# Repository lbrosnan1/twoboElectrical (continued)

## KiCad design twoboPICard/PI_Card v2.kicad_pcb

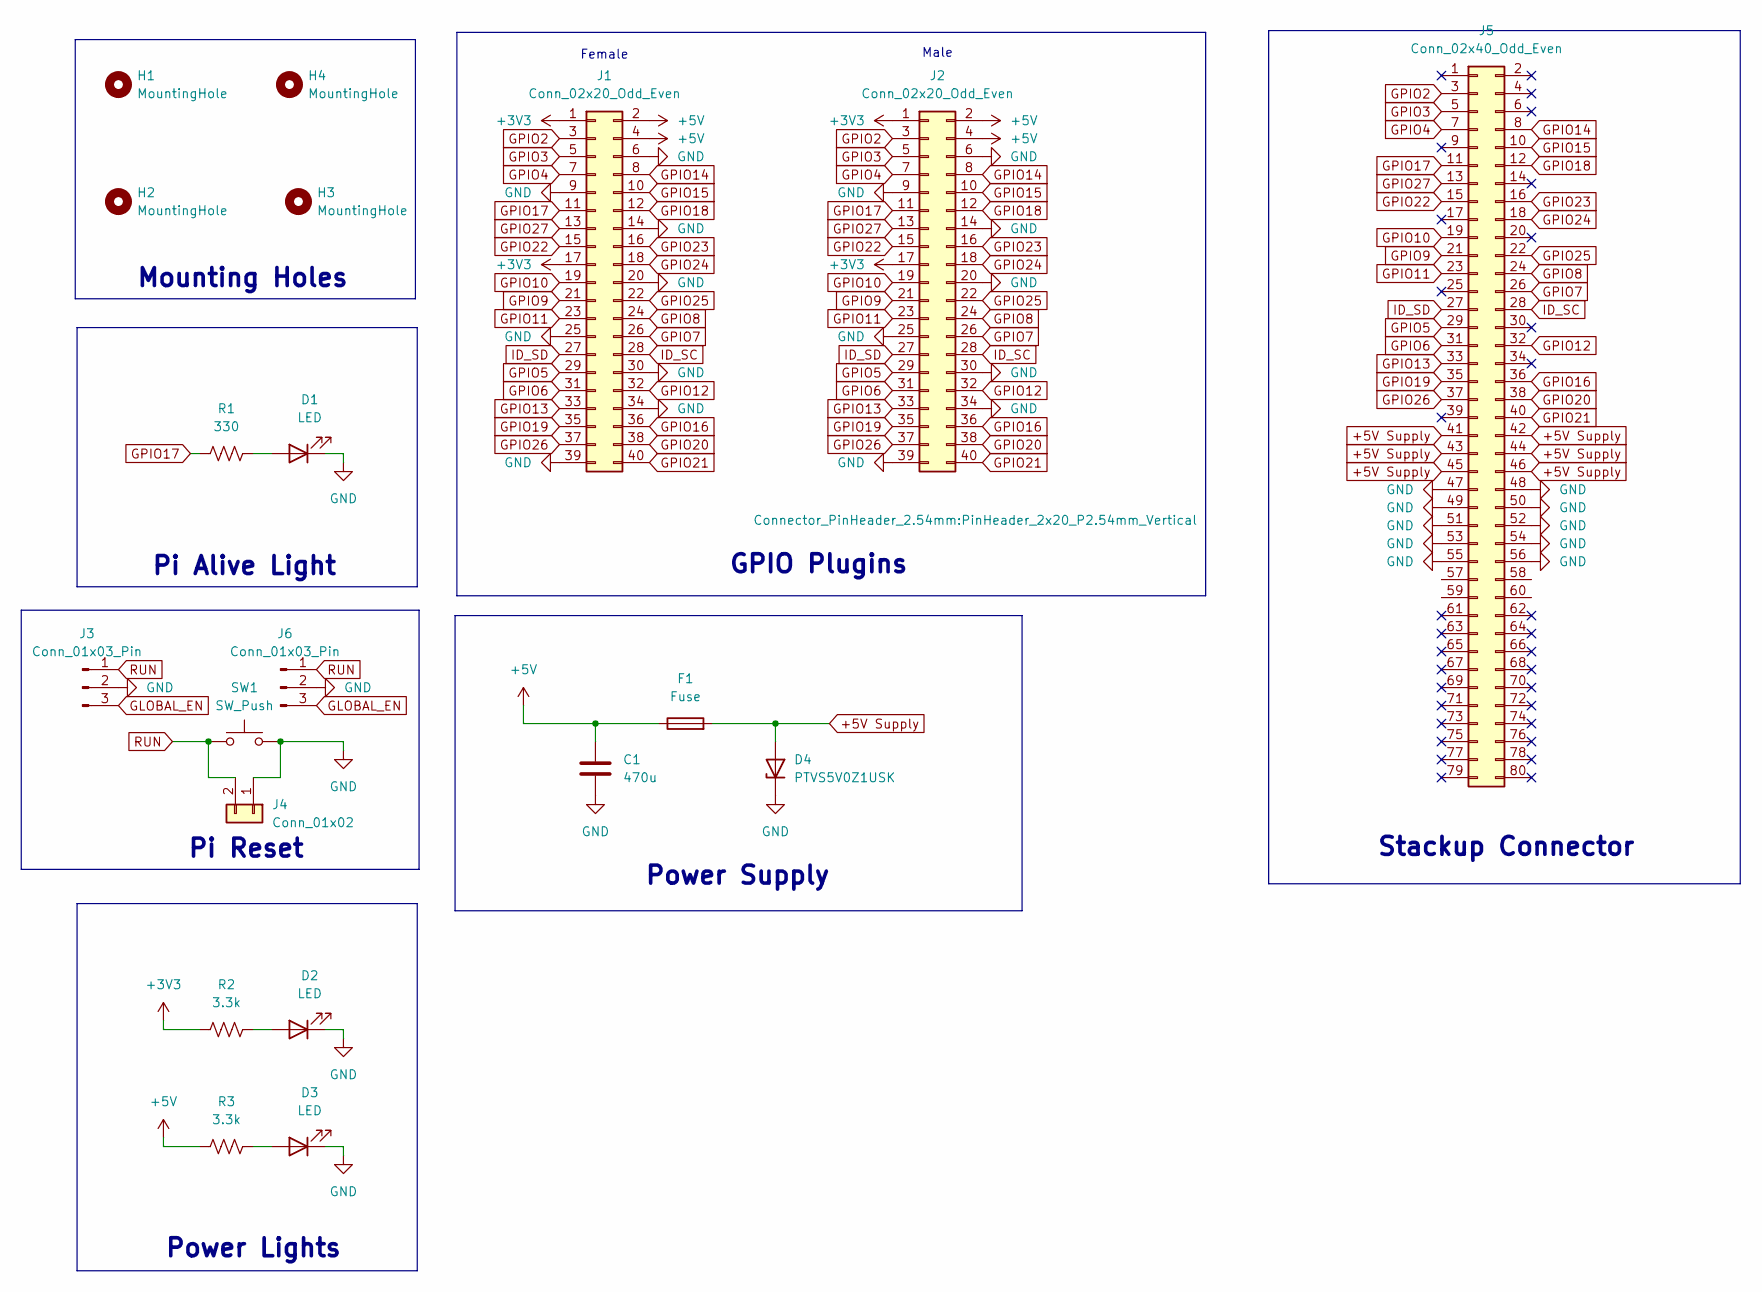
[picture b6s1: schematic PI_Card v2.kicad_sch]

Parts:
C1: 470u; CP_Radial_D10.0mm_P5.00mm
D1, D2, D3: LED; LED_D5.0mm
D4: PTVS5V0Z1USK; Nexperia_DSN1608-2_1.6x0.8mm
F1: Fuse; Fuseholder_Littelfuse_Nano2_154x_3D
H1, H2, H3, H4: MountingHole; MountingHole_3.2mm_M3
J1: Conn_02x20_Odd_Even; PinSocket_2x20_P2.54mm_Vertical
J2: Conn_02x20_Odd_Even; PinHeader_2x20_P2.54mm_Vertical
J3, J6: Conn_01x03_Pin; PinHeader_1x03_P2.54mm_Vertical
J4: Conn_01x02; JST_PH_B2B-PH-K_1x02_P2.00mm_Vertical
J5: Conn_02x40_Odd_Even; Samtec_HLE-140-02-L-DV-PE_2x40_P2.54mm_Horizontal
R1: 330; R_0805_2012Metric_Pad1.20x1.40mm_HandSolder
R2, R3: 3.3k; R_0805_2012Metric_Pad1.20x1.40mm_HandSolder
SW1: SW_Push; SW_PUSH_6mm

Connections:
+3V3: J1.1, J1.17, J2.1, J2.17, R2.1
+5V: C1.1, F1.1, J1.2, J1.4, J2.2, J2.4, R3.1
+5V Supply: D4.2 (A), F1.2, J5.41, J5.42, J5.43, J5.44, J5.45, J5.46
GLOBAL_EN: J3.3, J6.3
GND: C1.2, D1.1 (K), D2.1 (K), D3.1 (K), D4.1 (K), J1.6, J1.9, J1.14, J1.20, J1.25, J1.30, J1.34, J1.39, J2.6, J2.9, J2.14, J2.20, J2.25, J2.30, J2.34, J2.39, J3.2, J4.1, J5.47, J5.48, J5.49, J5.50, J5.51, J5.52, J5.53, J5.54, J5.55, J5.56, J6.2, SW1.2
GPIO2: J1.3, J2.3, J5.3
GPIO3: J1.5, J2.5, J5.5
GPIO4: J1.7, J2.7, J5.7
GPIO5: J1.29, J2.29, J5.29
GPIO6: J1.31, J2.31, J5.31
GPIO7: J1.26, J2.26, J5.26
GPIO8: J1.24, J2.24, J5.24
GPIO9: J1.21, J2.21, J5.21
GPIO10: J1.19, J2.19, J5.19
GPIO11: J1.23, J2.23, J5.23
GPIO12: J1.32, J2.32, J5.32
GPIO13: J1.33, J2.33, J5.33
GPIO14: J1.8, J2.8, J5.8
GPIO15: J1.10, J2.10, J5.10
GPIO16: J1.36, J2.36, J5.36
GPIO17: J1.11, J2.11, J5.11, R1.1
GPIO18: J1.12, J2.12, J5.12
GPIO19: J1.35, J2.35, J5.35
GPIO20: J1.38, J2.38, J5.38
GPIO21: J1.40, J2.40, J5.40
GPIO22: J1.15, J2.15, J5.15
GPIO23: J1.16, J2.16, J5.16
GPIO24: J1.18, J2.18, J5.18
GPIO25: J1.22, J2.22, J5.22
GPIO26: J1.37, J2.37, J5.37
GPIO27: J1.13, J2.13, J5.13
ID_SC: J1.28, J2.28, J5.28
ID_SD: J1.27, J2.27, J5.27
unnamed: D1.2 (A), R1.2
unnamed: D2.2 (A), R2.2
unnamed: D3.2 (A), R3.2
RUN: J3.1, J4.2, J6.1, SW1.1

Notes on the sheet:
Female
Power Supply
Pi Reset
GPIO Plugins
Stackup Connector
Power Lights
Pi Alive Light
Male
Mounting Holes

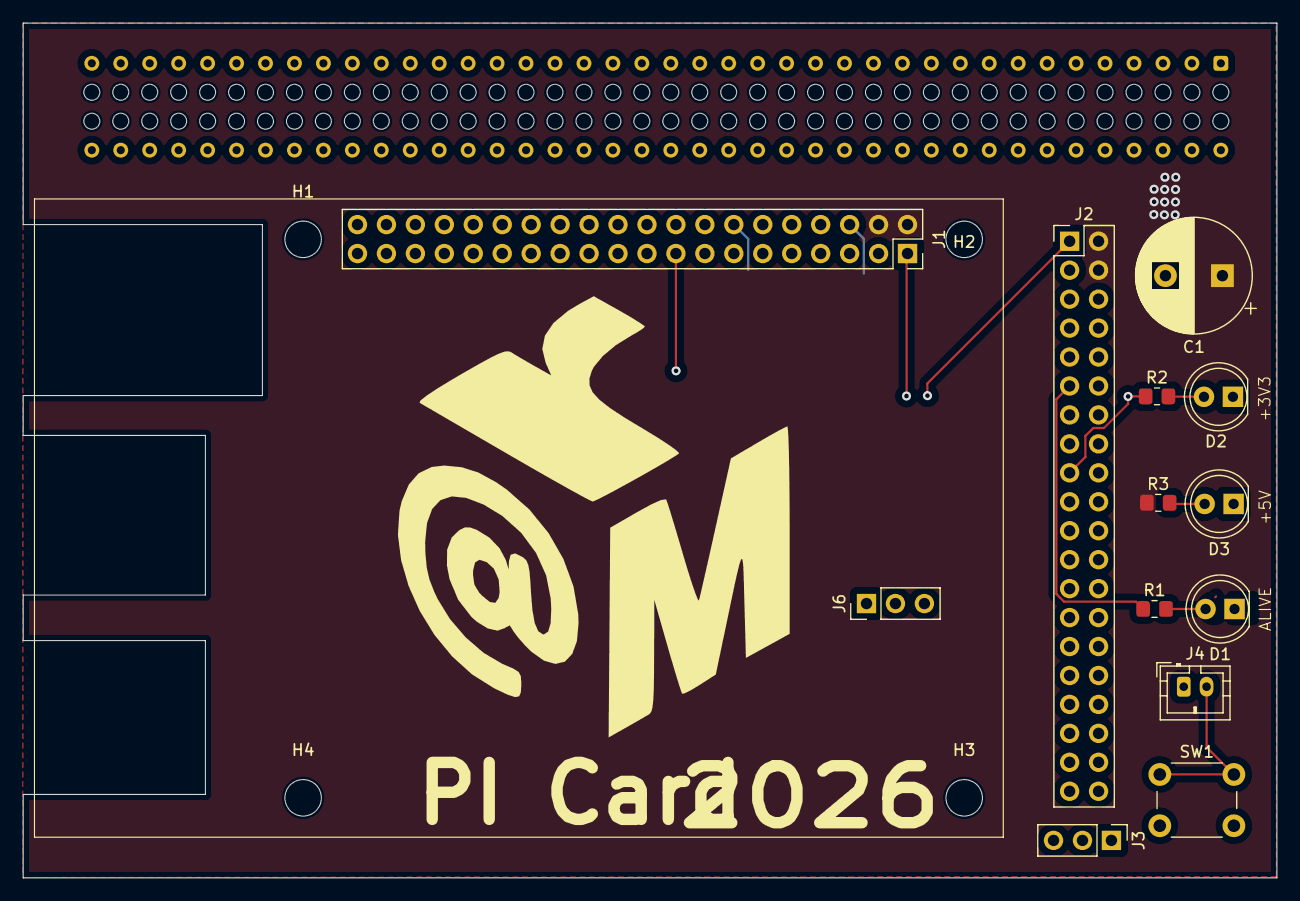
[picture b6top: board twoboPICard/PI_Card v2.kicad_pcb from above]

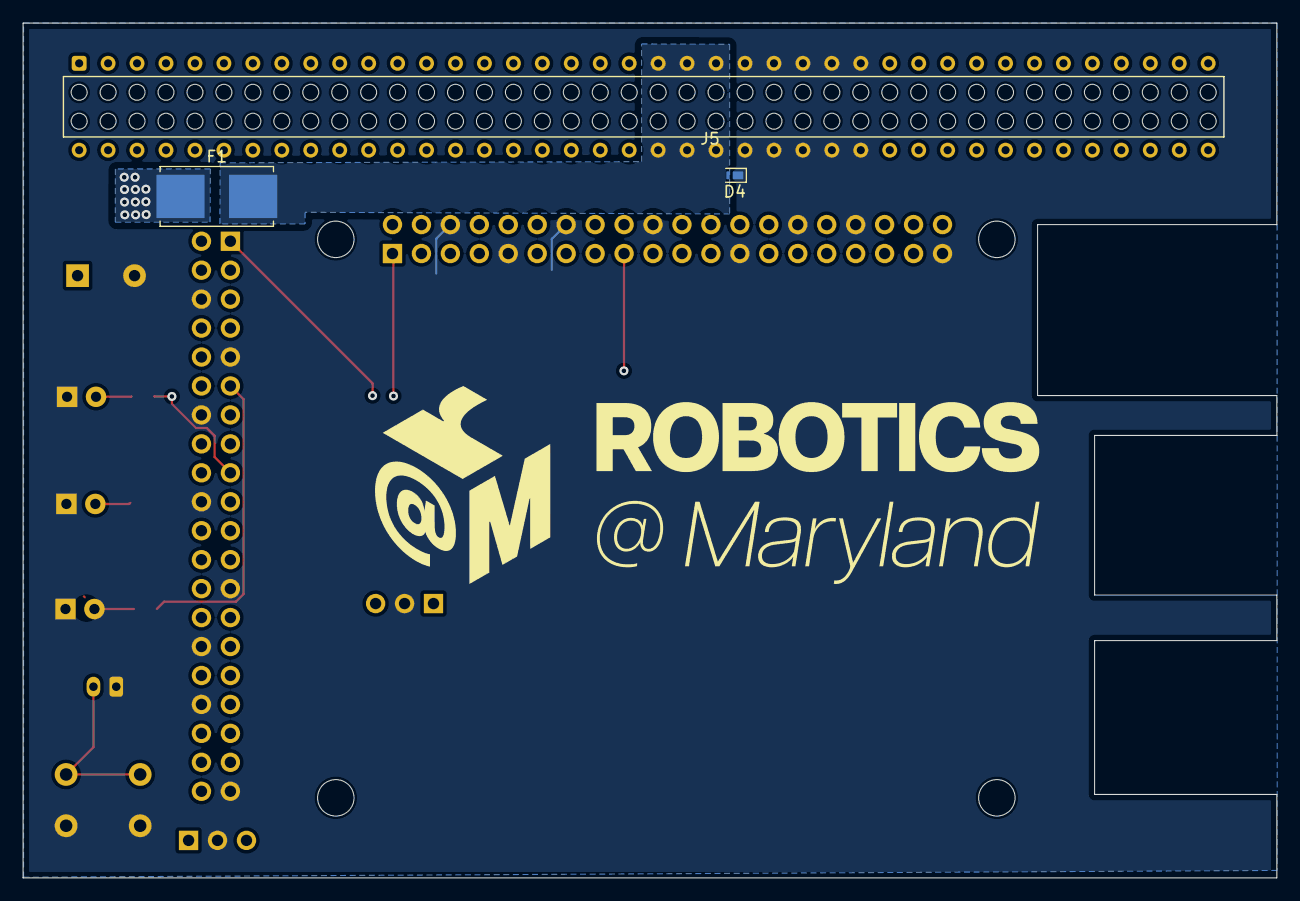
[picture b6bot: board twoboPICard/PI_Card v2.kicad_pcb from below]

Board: 4 copper layers, 110.0 x 75.0 mm, 20 parts (3 on the bottom side), 37 nets.

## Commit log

2026-02-01 twobo power card(i accidentally named it qubo)
2026-02-01 changed name to twobo
2026-02-01 Added PI Card
    Thank god...
2026-02-01 Added Schematic
2026-02-02 Fixed Fuse Positioning & Unconnected Nets
2026-02-05 Added connector to power card
2026-02-08 Reverted broken name change
2026-03-05 Found this Version...?
2026-03-15 Repositioned Connections
2026-03-15 Added I2C & Reset Toggle
2026-03-15 Cut off Arms
2026-03-15 Added Thruster Card
2026-03-22 Added LED Board
2026-03-22 Thruster card - added PWM Driver, esc and removed eurocard
2026-03-22 Thruster card
    added the stack up connector.
    first iteration of routing
2026-03-23 Changed location of thruster connector
2026-03-26 added power routes
2026-03-27 no_change
2026-04-05 pi card start
    still needs resistors and capacitors put in, confirmation of pi 5v converter set up, and general clean up
2026-04-06 power card update
    put the resistors/capacitors in and added in the traces, also added the two switch jsts.
2026-04-13 Repositioned Thruster Board Connector
2026-04-13 Added Silkscreen
2026-04-17 Viewed Files
2026-04-17 Changed Stackup to Pinheader
2026-04-17 Repositioned Mounting Holes
2026-04-19 twoBo thruster
2026-04-19 Changed connector orientation
2026-04-21 Added Silkscreen, 12V Drops, Holes
2026-04-23 Kurt Review
2026-04-26 Added I2C Pull Up Resistors
2026-05-03 Created Production Files
